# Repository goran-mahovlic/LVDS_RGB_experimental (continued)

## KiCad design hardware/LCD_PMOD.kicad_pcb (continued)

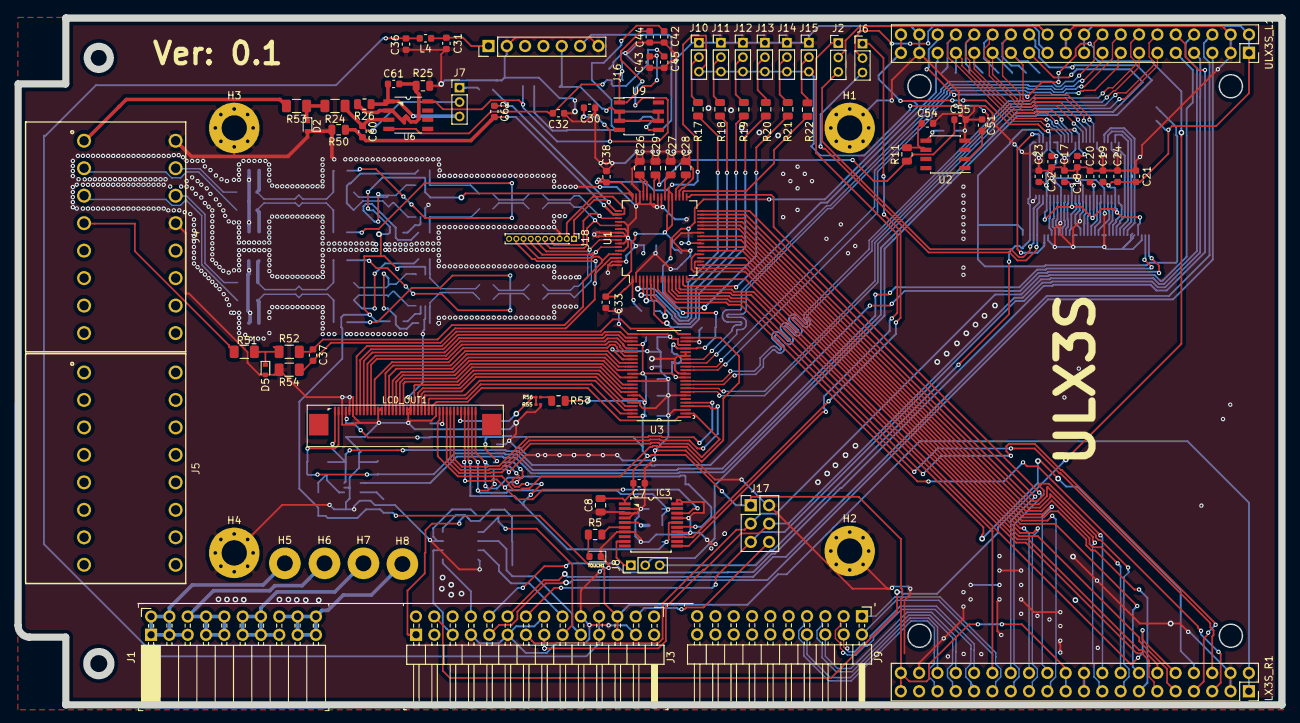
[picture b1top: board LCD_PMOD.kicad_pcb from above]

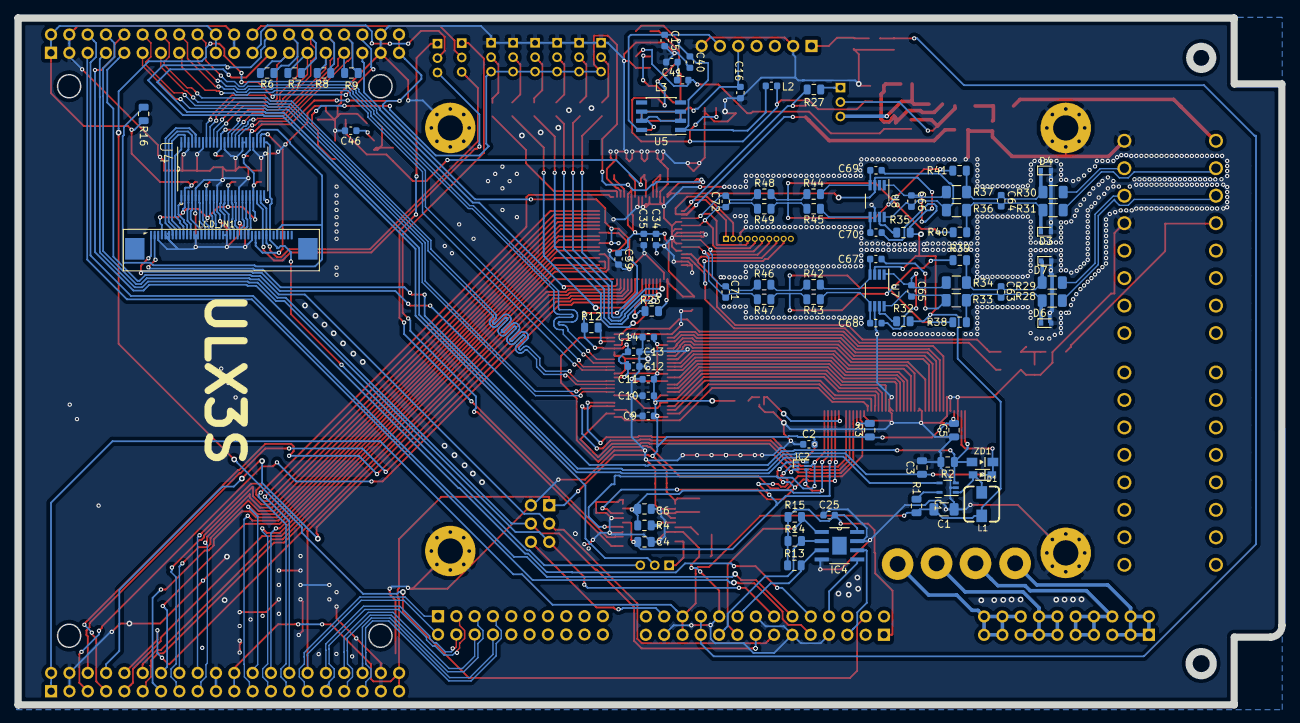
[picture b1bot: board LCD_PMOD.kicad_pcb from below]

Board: 2 copper layers, 175.3 x 95.2 mm, 174 parts (85 on the bottom side), 199 nets.

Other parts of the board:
C46: 1u; C_0603_1608Metric
L4: 6.8uF; R_0603_1608Metric

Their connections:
GND: C46.2; also elsewhere on the board
unnamed 159: C46.1; also elsewhere on the board

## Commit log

2020-01-20 adding initial work in progress schematics/PCB/3D
2020-01-21 Adding pdf
2020-01-21 Ading pictures
2020-01-21 Ading project changes
2020-01-22 Adding parts
2020-01-22 Adding decoupling capacitors, termination resoistors for LVDS IN
2020-01-22 Adding pin enable to ADS8556IPM
2020-01-22 Adding selection resistors
2020-01-23 Adding REF5025
2020-01-23 Adding THS4032
2020-01-23 Adding new PDF
2020-01-23 Adding buffe ramp , REF amp, DIFF amp
2020-01-23 Drawing and adding AMC1304M
2020-01-23 Adding AMC1304 to the board
2020-01-25 Adding Bias_PS from dcm220
2020-01-27 Adding ULX3S connections
2020-01-27 Assigning footprints
2020-01-28 Adding chip power down fix - removing ADS8556 chip
2020-01-28 Adding ads8586s
2020-01-28 Adding ads8586s to shematics
2020-01-29 Fixing ADS8586 IN/OUT
2020-01-29 Partially connecting ads8586s
2020-01-29 Adding last known changes to shematics
2020-01-29 Adding part OPA187
2020-01-29 Renaming wires
2020-01-29 Adding new shematics
2020-02-07 Fix TBA1E
2020-02-07 Routing board
2020-02-08 Before AGND - GND
2020-02-12 Finishing routing
2020-02-12 Adding 3D parts - adding puctures
2020-02-12 Adding MDS01
2020-02-12 Adding pcb changes to PBC
2020-02-12 Adding new pictures
2020-02-12 Rerouting
2020-02-12 adding pictures to readme
2020-02-12 Change README
2020-02-12 Changing back picture
2020-02-12 Adding DIB_V1 connectors
2020-02-12 New pdf
2020-02-13 Moving ULX3S connector lower
2020-02-15 Adding Gerbers
2020-02-15 Adding better pictures
2020-02-15 Board V0.1
2020-02-15 Adding version number
2020-02-17 Adding initial BOM list
